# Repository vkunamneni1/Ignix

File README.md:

# Ignix

Ignix is a PCB-built rhythm toy that lights up an LED and buzzes a motor with button presses, allowing users to tap out customizable light and haptic pulses (through the use of a potentiometer-controlled timer circuit).

## Schematic

## PCB

## Features
- Powered by a SINGLE CR2032 battery
- LED that lights up on button press
- DC Motor that buzzes on button press
- Adjustable light and buzz length
- Musical images on front
- Schematic on back
- Hack Club logo!

## BOM
- 1 Battery holder
- 1 10µF Capacitor
- 1 LED
- 1 DC Motor
- 1 NPN Transistor
- 1 PNP Transistor
- 3 4.7kΩ Resistors
- 1 220Ω Resistor
- 1 47kΩ Potentiometer
- 1 Push Button
  
slack: `@veds`

Made as a part of http://solder.hackclub.com/!

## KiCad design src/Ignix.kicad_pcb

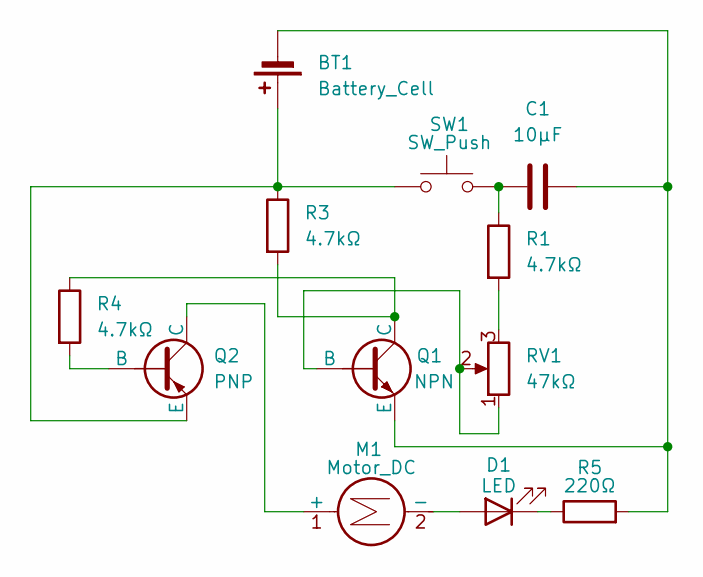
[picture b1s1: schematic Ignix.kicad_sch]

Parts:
BT1: Battery_Cell; BatteryHolder_Keystone_3034_1x20mm
C1: 10µF; CP_Radial_D8.0mm_P5.00mm
D1: LED; LED_D5.0mm
M1: Motor_DC; PinHeader_1x02_P2.54mm_Vertical
Q1: NPN; TO-92L_HandSolder
Q2: PNP; TO-92L_HandSolder
R1, R3, R4: 4.7kΩ; R_Axial_DIN0207_L6.3mm_D2.5mm_P7.62mm_Horizontal
R5: 220Ω; R_Axial_DIN0207_L6.3mm_D2.5mm_P7.62mm_Horizontal
RV1: 47kΩ; Potentiometer_Vishay_T73YP_Vertical
SW1: SW_Push; SW_PUSH_6mm

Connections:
unnamed: BT1.1 (+), Q2.3 (E), R3.1, SW1.1
unnamed: BT1.2 (-), C1.2, Q1.3 (E), R5.2
unnamed: C1.1, R1.1, SW1.2
unnamed: D1.2 (A), M1.2 (-)
unnamed: D1.1 (K), R5.1
unnamed: M1.1 (+), Q2.1 (C)
unnamed: Q1.2 (B), RV1.1, RV1.2
unnamed: Q1.1 (C), R3.2, R4.1
unnamed: Q2.2 (B), R4.2
unnamed: R1.2, RV1.3

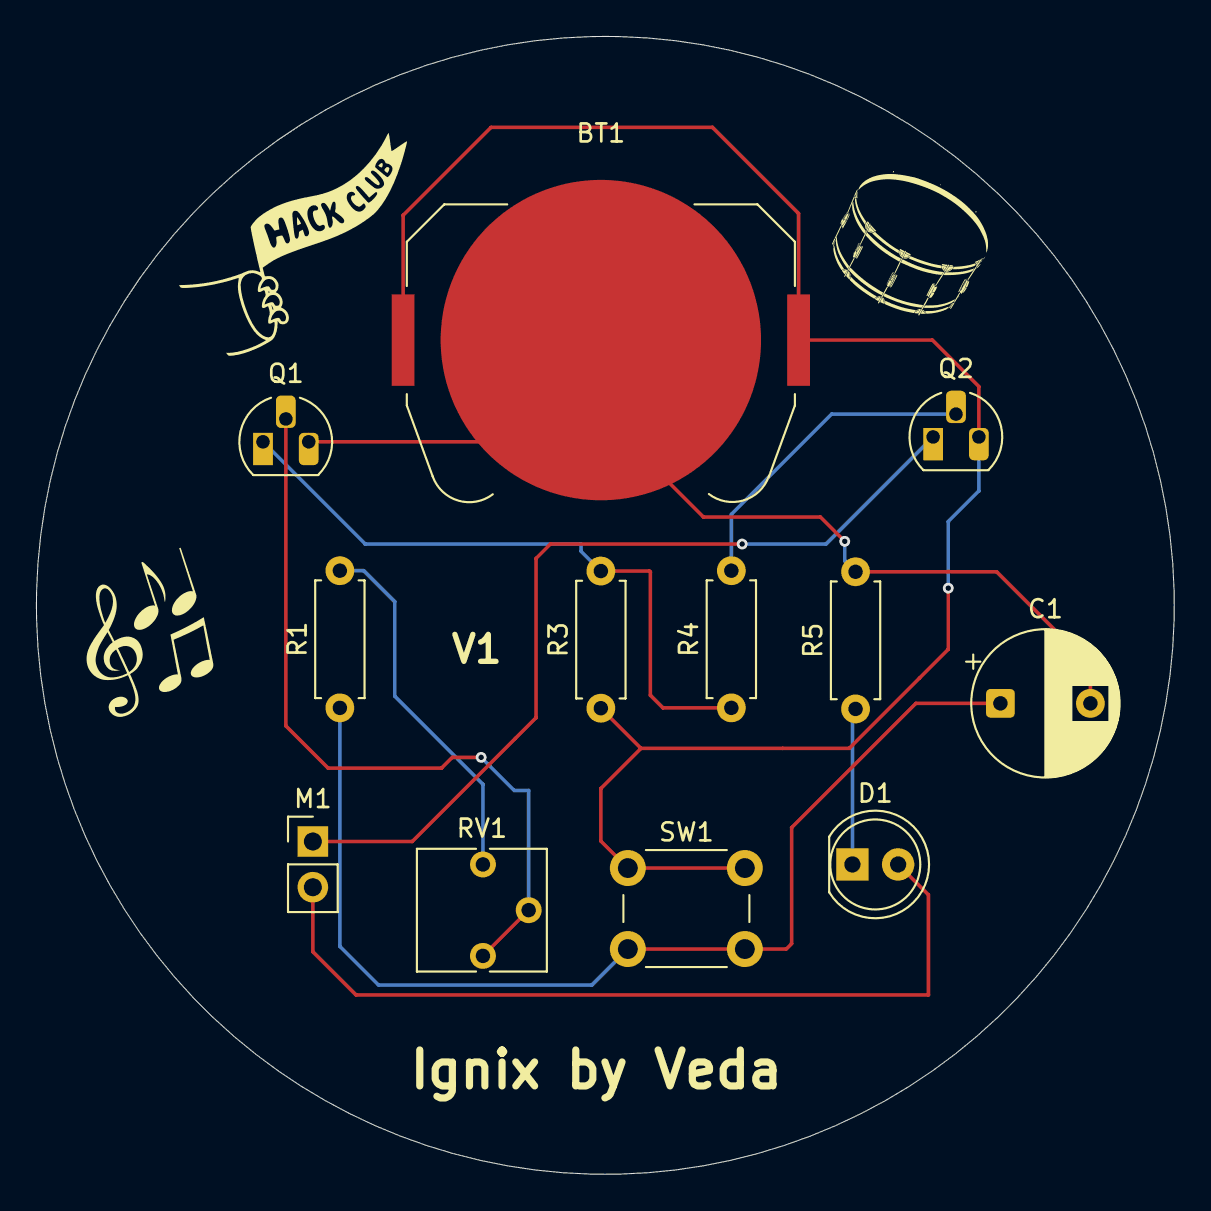
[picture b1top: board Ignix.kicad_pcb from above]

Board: 2 copper layers, 63.2 x 63.2 mm, 12 parts (0 on the bottom side), 10 nets.

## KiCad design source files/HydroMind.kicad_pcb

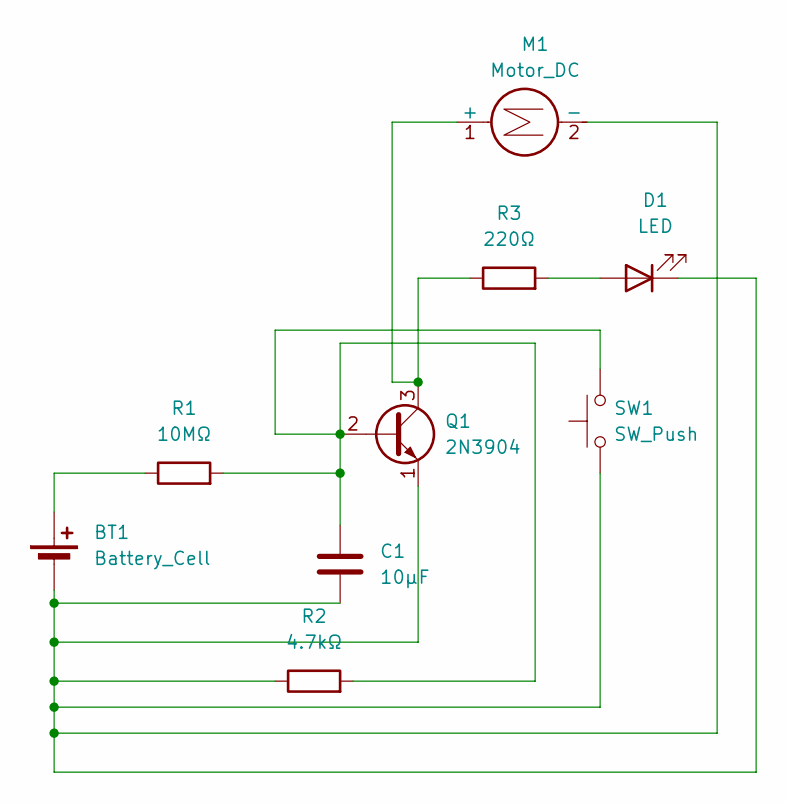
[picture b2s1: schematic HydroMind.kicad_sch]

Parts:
BT1: Battery_Cell; BatteryHolder_Keystone_3034_1x20mm
C1: 10µF; CP_Radial_D8.0mm_P5.00mm
D1: LED; LED_D5.0mm
M1: Motor_DC; PinHeader_1x02_P2.54mm_Vertical
Q1: 2N3904; TO-92L_HandSolder
R1: 10MΩ; R_Axial_DIN0207_L6.3mm_D2.5mm_P7.62mm_Horizontal
R2: 4.7kΩ; R_Axial_DIN0207_L6.3mm_D2.5mm_P7.62mm_Horizontal
R3: 220Ω; R_Axial_DIN0207_L6.3mm_D2.5mm_P7.62mm_Horizontal
SW1: SW_Push; SW_PUSH_6mm

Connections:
unnamed: BT1.1 (+), R1.1
unnamed: BT1.2 (-), C1.2, D1.1 (K), M1.2 (-), Q1.1 (E), R2.1, SW1.1
unnamed: D1.2 (A), R3.2
unnamed: M1.1 (+), Q1.3 (C), R3.1
unnamed: C1.1, Q1.2 (B), R1.2, R2.2, SW1.2

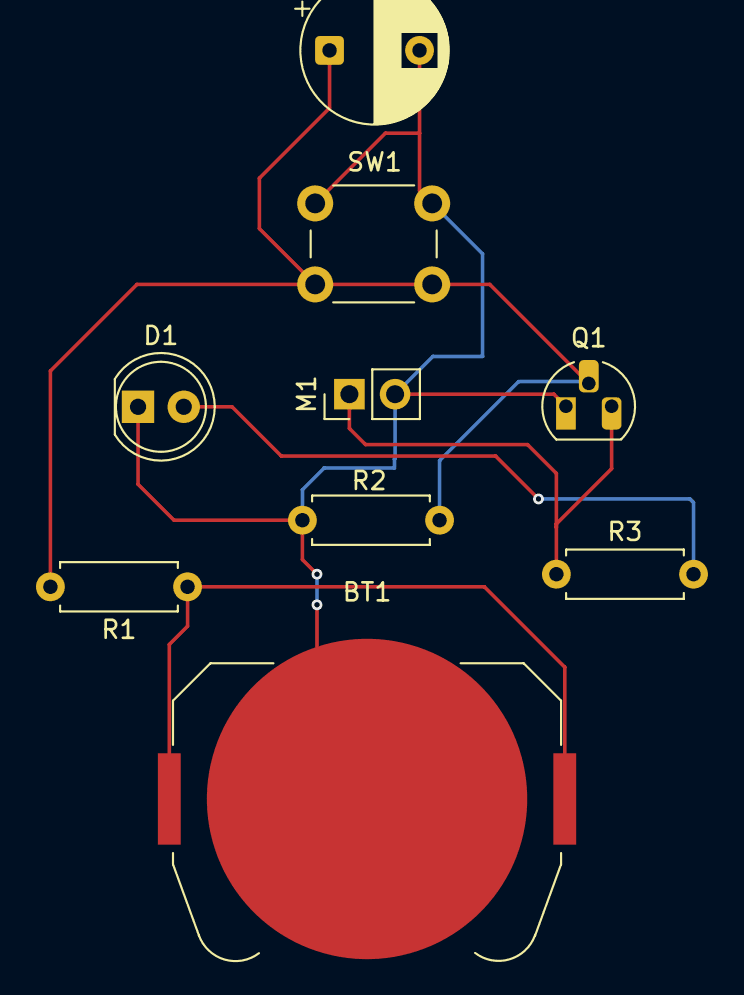
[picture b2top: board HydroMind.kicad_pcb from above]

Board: 2 copper layers, 9 parts (0 on the bottom side), 5 nets.

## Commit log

2025-05-22 Added source files folder
2025-05-22 added all source files
2025-05-24 cleanup
2025-05-24 completed schematic and pcb design (iteration 1)
2025-05-24 removed sf
2025-05-24 redid pcb
2025-05-29 removed HydroMind files
2025-05-29 removed ds
2025-05-30 added pcb / schem files
2025-05-30 removed
2025-05-30 finished schem and pcb
2025-05-30 removed junk
2025-05-30 removed junk and updated FINAL pcb / schem
2025-05-30 formatted and added to repo
2025-05-30 added screenshots
2025-05-31 removed ds store
2025-05-31 revised repo
2025-05-31 flipped battery
2026-01-09 Refine Ignix description in README.md
    Removed unnecessary introductory phrase from the description.
